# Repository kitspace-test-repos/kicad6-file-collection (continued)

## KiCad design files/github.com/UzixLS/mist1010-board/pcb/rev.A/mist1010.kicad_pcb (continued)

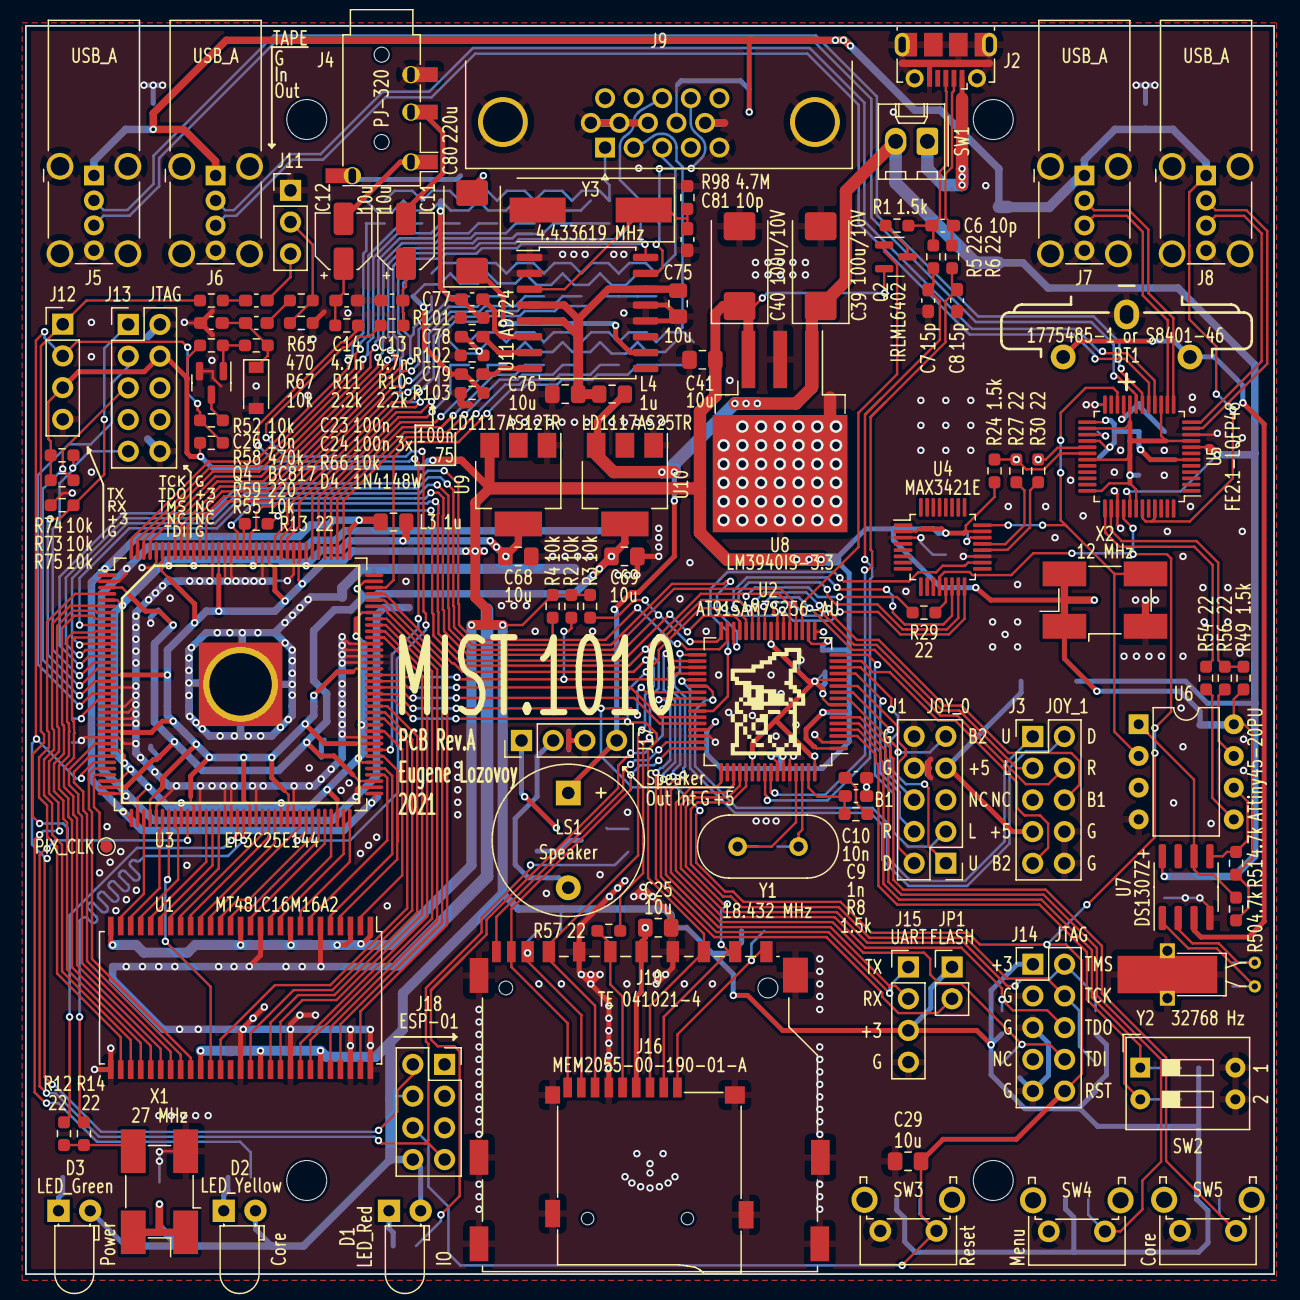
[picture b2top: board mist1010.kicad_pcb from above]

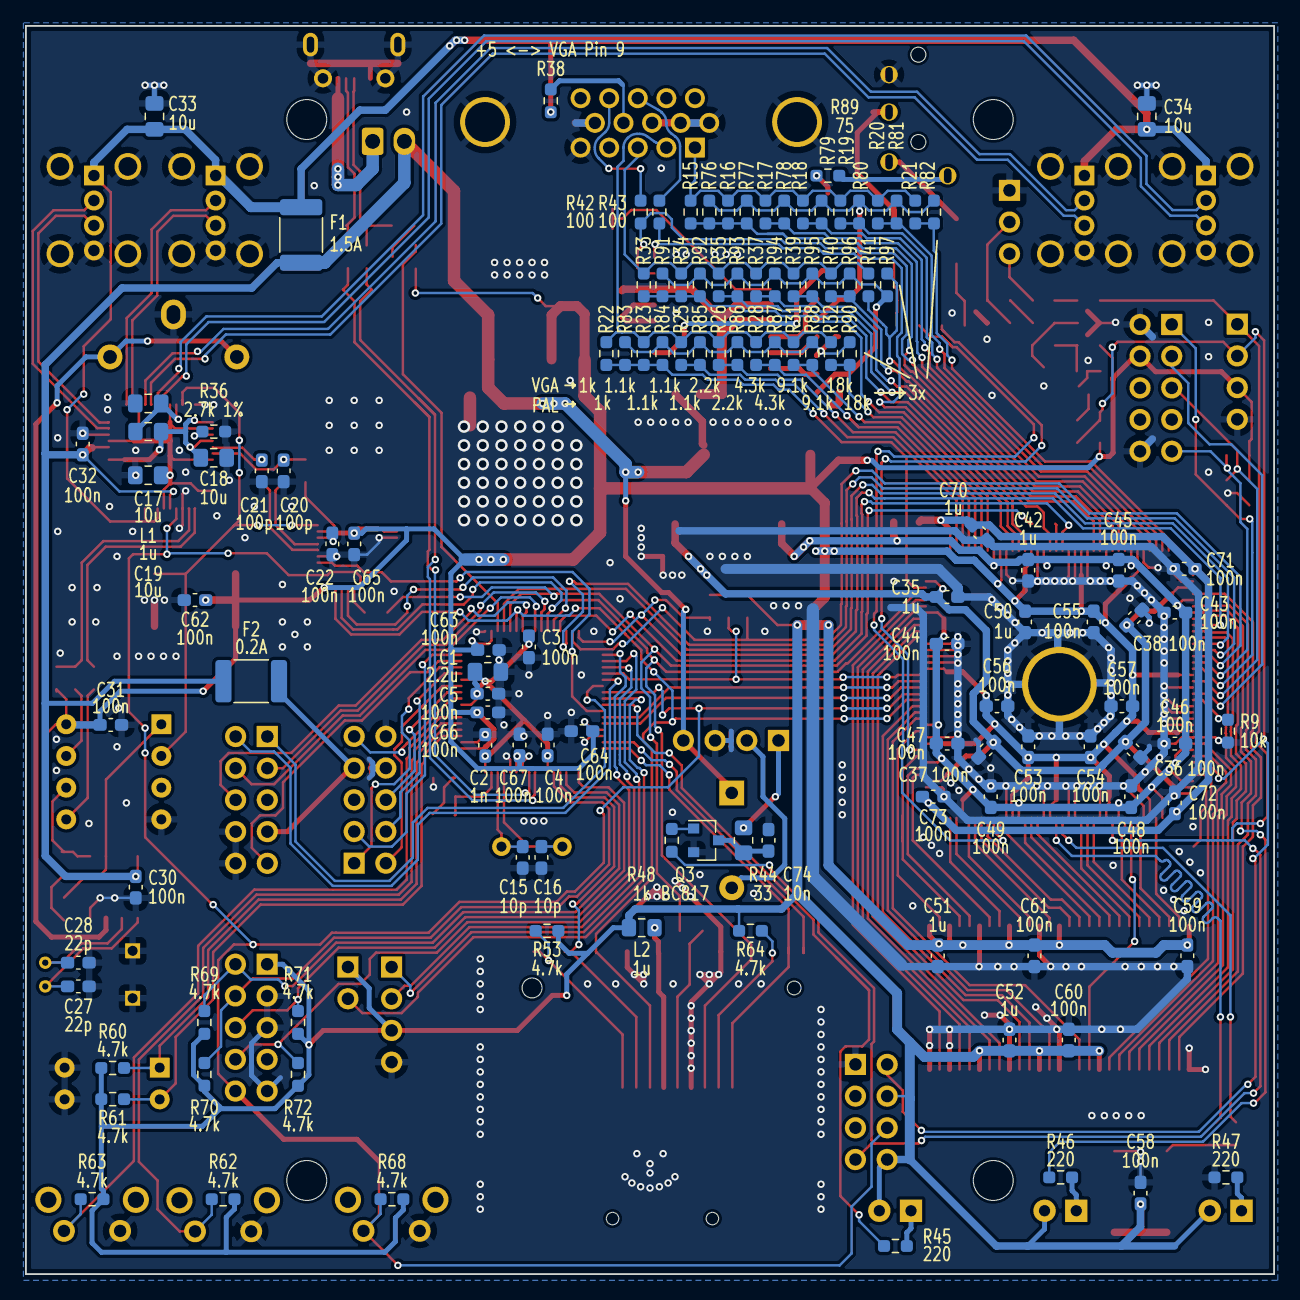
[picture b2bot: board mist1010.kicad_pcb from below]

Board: 2 copper layers, 100.0 x 100.0 mm, 242 parts (124 on the bottom side), 201 nets.

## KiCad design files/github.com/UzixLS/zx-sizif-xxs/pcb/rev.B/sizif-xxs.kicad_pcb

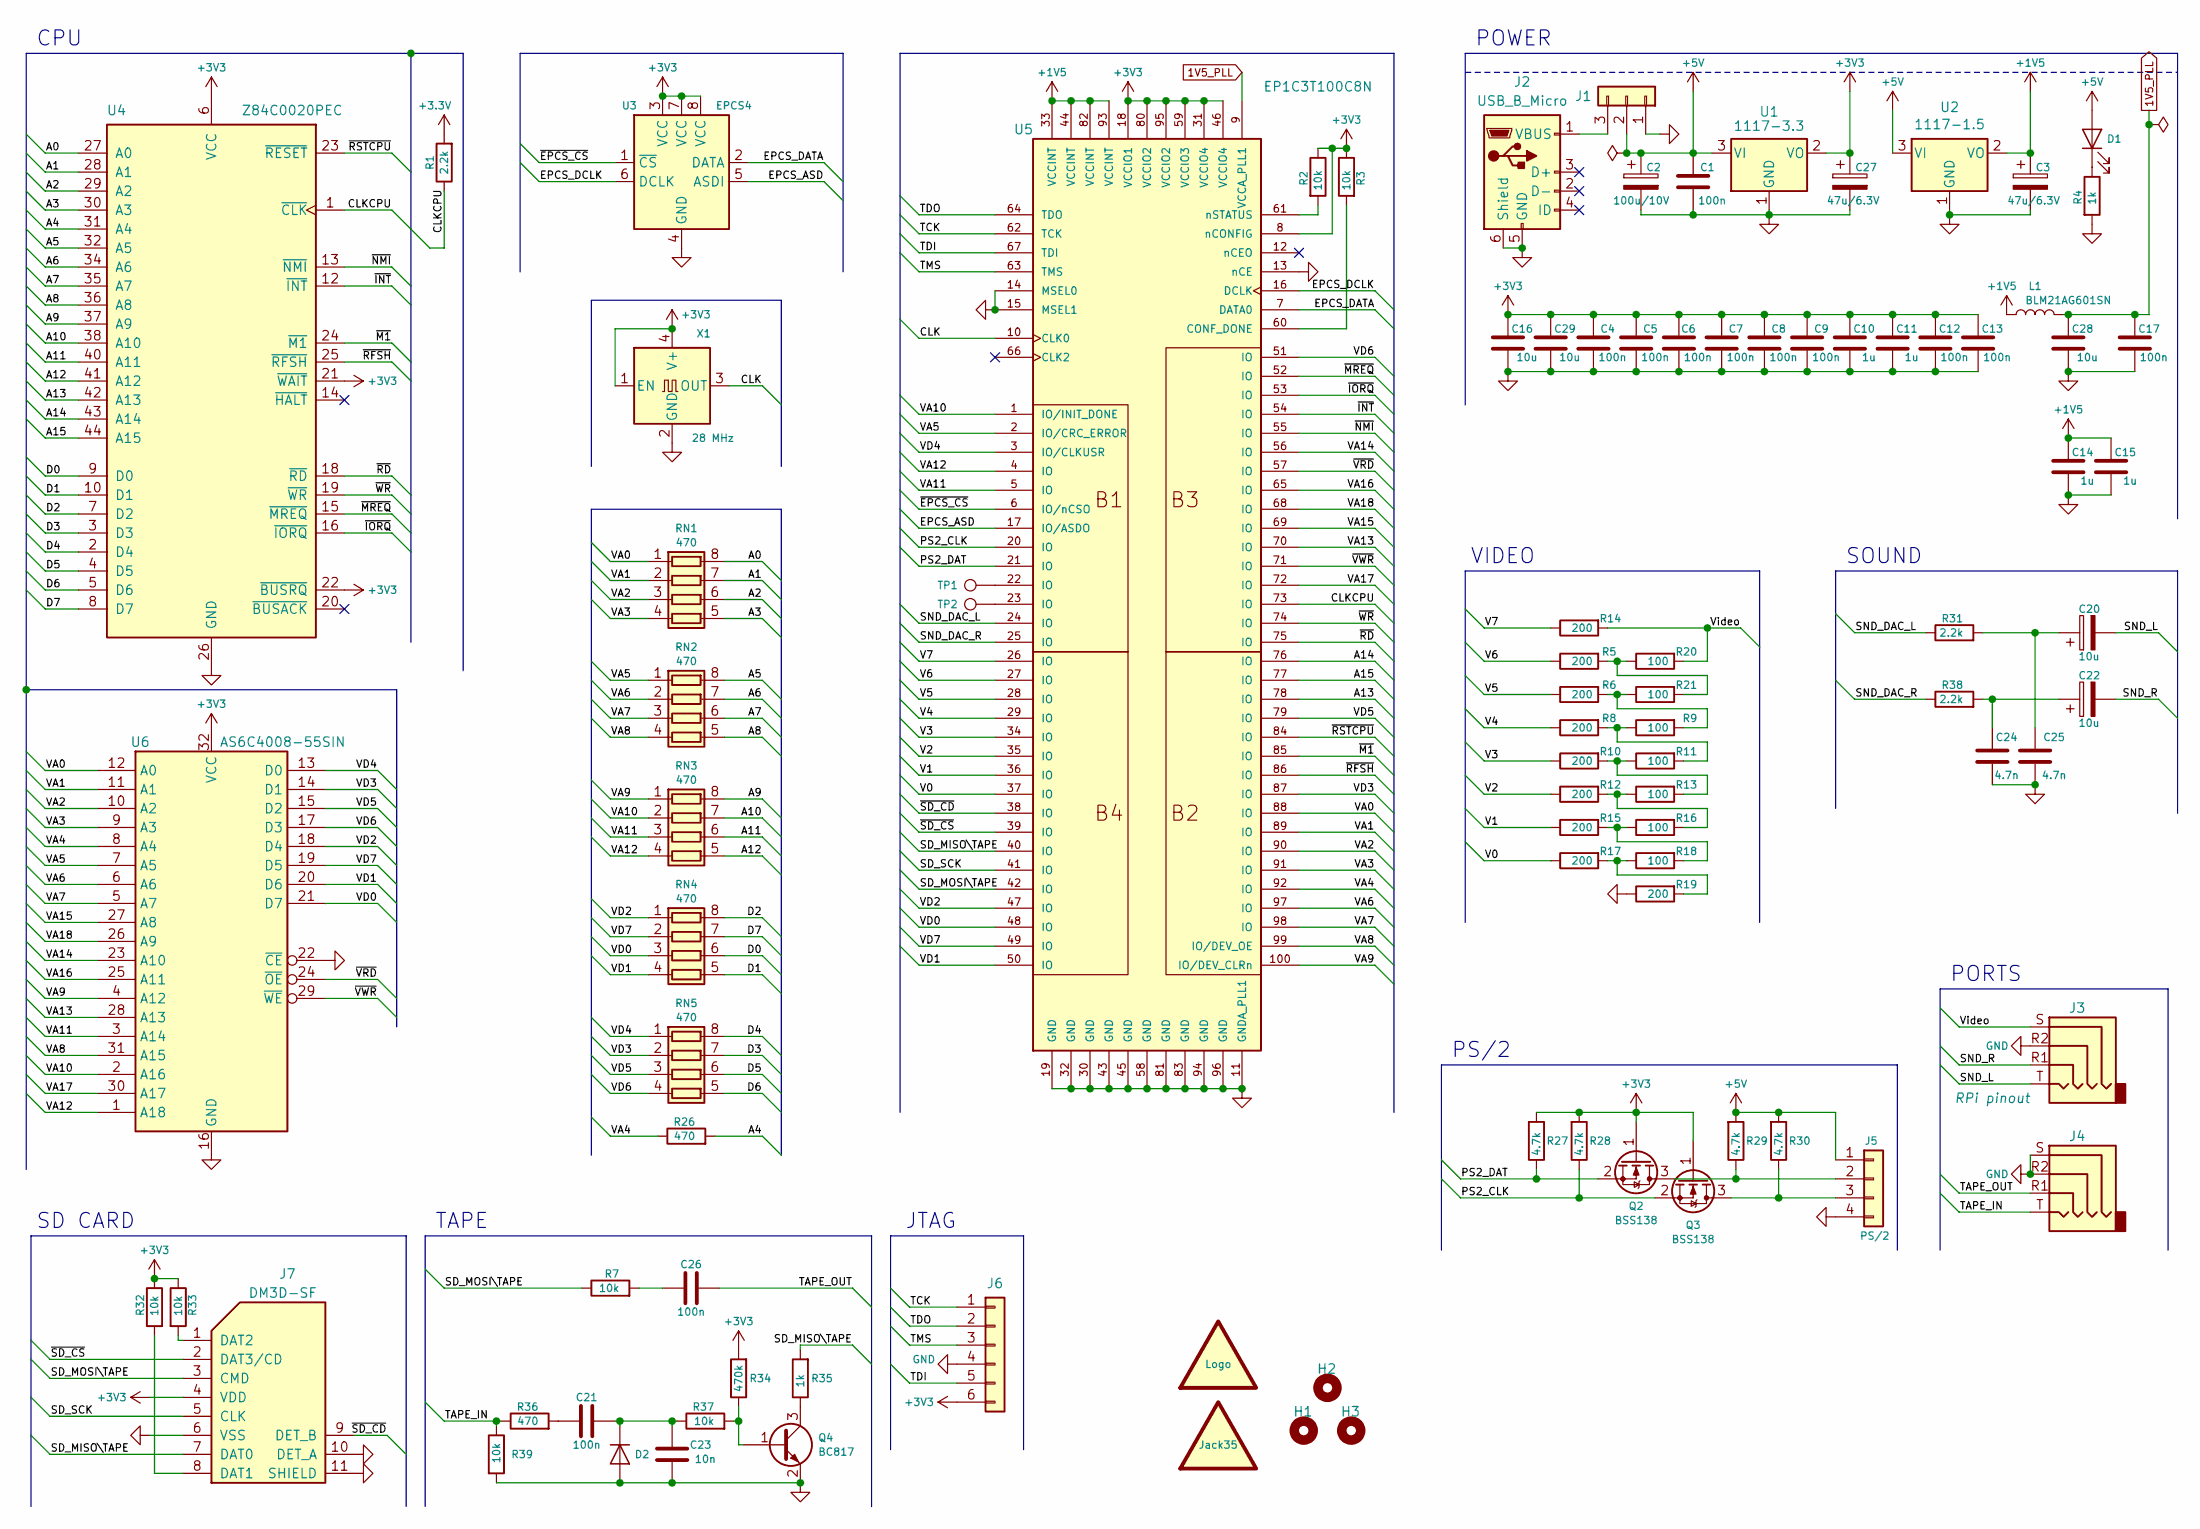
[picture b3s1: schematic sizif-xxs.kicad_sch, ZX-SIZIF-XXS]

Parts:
C1, C4, C6, C7, C8, C9, C12, C13, C17, C21, C26: 100n; C_0603_1608Metric_Pad1.08x0.95mm_HandSolder
C2: 100u/10V; CP_EIA-7343-31_Kemet-D_Pad2.25x2.55mm_HandSolder
C3, C27: 47u/6.3V; CP_EIA-3528-21_Kemet-B_Pad1.50x2.35mm_HandSolder
C5: 100n; C_0805_2012Metric_Pad1.18x1.45mm_HandSolder
C10, C11, C14, C15: 1u; C_0603_1608Metric_Pad1.08x0.95mm_HandSolder
C16, C28, C29: 10u; C_0805_2012Metric_Pad1.18x1.45mm_HandSolder
C20, C22: 10u; CP_EIA-3216-18_Kemet-A_Pad1.58x1.35mm_HandSolder
C23: 10n; C_0603_1608Metric_Pad1.08x0.95mm_HandSolder
C24, C25: 4.7n; C_0603_1608Metric_Pad1.08x0.95mm_HandSolder
D1: LED; LED_D4.0mm
D2: 1N4148W; D_SOD-123
H1, H2, H3: MountingHole; MountingHole_2.7mm_M2.5_dk5.0mm_Mask
J1: Pin header 1x3 Pitch=2.54mm; PinHeader_1x03_P2.54mm_Vertical
J2: USB_B_Micro; USB_Micro-B_Molex-105017-0001
J3, J4: PJ-320; PJ-320A_D
J5: Pin header 1x4 Pitch=2.54mm; PinHeader_1x04_P2.54mm_Vertical
J6: Solder points; PinPoints_1x06_P1.27mm
J7: DM3D-SF; microSD_HC_Hirose_DM3D-SF
L1: BLM21AG601SN; L_0805_2012Metric_Pad1.15x1.40mm_HandSolder
LOGO1: graphic; black-mage-9.6x6.5
LOGO2: Jack35; jack35_4pin
Q2, Q3: BSS138; SOT-23
Q4: BC817; SOT-23
R1, R31, R38: 2.2k; R_0603_1608Metric_Pad0.98x0.95mm_HandSolder
R2, R3, R7, R32, R33, R37, R39: 10k; R_0603_1608Metric_Pad0.98x0.95mm_HandSolder
R4, R35: 1k; R_0603_1608Metric_Pad0.98x0.95mm_HandSolder
R5, R6, R8, R10, R12, R14, R15, R17, R19: 200; R_0603_1608Metric_Pad0.98x0.95mm_HandSolder
R9, R11, R13, R16, R18, R20, R21: 100; R_0603_1608Metric_Pad0.98x0.95mm_HandSolder
R26, R36: 470; R_0603_1608Metric_Pad0.98x0.95mm_HandSolder
R27, R28, R29, R30: 4.7k; R_0603_1608Metric_Pad0.98x0.95mm_HandSolder
R34: 470k; R_0603_1608Metric_Pad0.98x0.95mm_HandSolder
RN1, RN2, RN3, RN4, RN5: 470; R_Array_Convex_4x0603
TP1, TP2: TestPoint; TestPoint_Pad_D1.0mm
U1: 1117-3.3; SOT-223-3_TabPin2
U2: 1117-1.5; SOT-223-3_TabPin2
U3: EPCS4; SOIC-8_3.9x4.9mm_P1.27mm
U4: Z84C0020PEC; TQFP-44_14x14mm_P0.8mm
U5: EP1C3T100C8N; TQFP-100_14x14mm_P0.5mm
U6: AS6C4008-55SIN; SSOP-32_11.305x20.495mm_P1.27mm
X1: 28 MHz; Oscillator_SMD_SeikoEpson_SG8002CA-4Pin_7.0x5.0mm

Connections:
1V5_PLL: C17.2, C28.2, L1.2, U5.9 (VCCA_PLL1)
+1V5: C3.1, C14.1, C15.2, L1.1, U2.2 (VO), U5.33 (VCCINT), U5.44 (VCCINT), U5.82 (VCCINT), U5.93 (VCCINT)
+5V: C1.2, C2.1, D1.2 (A), J1.2, J5.1, R29.2, R30.2, U1.3 (VI), U2.3 (VI)
/A0: RN1.8 (R1.2), U4.27 (A0)
/A1: RN1.7 (R2.2), U4.28 (A1)
/A2: RN1.6 (R3.2), U4.29 (A2)
/A3: RN1.5 (R4.2), U4.30 (A3)
/A4: R26.2, U4.31 (A4)
/A5: RN2.8 (R1.2), U4.32 (A5)
/A6: RN2.7 (R2.2), U4.34 (A6)
/A7: RN2.6 (R3.2), U4.35 (A7)
/A8: RN2.5 (R4.2), U4.36 (A8)
/A9: RN3.8 (R1.2), U4.37 (A9)
/A10: RN3.7 (R2.2), U4.38 (A10)
/A11: RN3.6 (R3.2), U4.40 (A11)
/A12: RN3.5 (R4.2), U4.41 (A12)
/A13: U4.42 (A13), U5.78 (IO)
/A14: U4.43 (A14), U5.76 (IO)
/A15: U4.44 (A15), U5.77 (IO)
/CLK: U5.10 (CLK0), X1.3 (OUT)
/CLKCPU: R1.1, U4.1 (~CLK~), U5.73 (IO)
/D0: RN4.6 (R3.2), U4.9 (D0)
/D1: RN4.5 (R4.2), U4.10 (D1)
/D2: RN4.8 (R1.2), U4.7 (D2)
/D3: RN5.7 (R2.2), U4.3 (D3)
/D4: RN5.8 (R1.2), U4.2 (D4)
/D5: RN5.6 (R3.2), U4.4 (D5)
/D6: RN5.5 (R4.2), U4.5 (D6)
/D7: RN4.7 (R2.2), U4.8 (D7)
/EPCS_ASD: U3.5 (ASDI), U5.17 (IO/ASDO)
/EPCS_DATA: U3.2 (DATA), U5.7 (DATA0)
/EPCS_DCLK: U3.6 (DCLK), U5.16 (DCLK)
/PS2_CLK: Q3.2 (S), R28.1, U5.20 (IO)
/PS2_DAT: Q2.2 (S), R27.1, U5.21 (IO)
/SD_MISO\TAPE: J7.7 (DAT0), R35.2, U5.40 (IO)
/SD_MOSI\TAPE: J7.3 (CMD), R7.1, U5.42 (IO)
/SD_SCK: J7.5 (CLK), U5.41 (IO)
/SND_DAC_L: R31.1, U5.24 (IO)
/SND_DAC_R: R38.1, U5.25 (IO)
/SND_L: C20.2, J3.T
/SND_R: C22.2, J3.R1
/TAPE_IN: J4.T, R36.1, R39.1
/TAPE_OUT: C26.1, J4.R1
/TCK: J6.1, U5.62 (TCK)
/TDI: J6.5, U5.67 (TDI)
/TDO: J6.2, U5.64 (TDO)
/TMS: J6.3, U5.63 (TMS)
/V0: R17.1, U5.37 (IO)
/V1: R15.1, U5.36 (IO)
/V2: R12.1, U5.35 (IO)
/V3: R10.1, U5.34 (IO)
/V4: R8.1, U5.29 (IO)
/V5: R6.1, U5.28 (IO)
/V6: R5.1, U5.27 (IO)
/V7: R14.1, U5.26 (IO)
/VA0: RN1.1 (R1.1), U5.88 (IO), U6.12 (A0)
/VA1: RN1.2 (R2.1), U5.89 (IO), U6.11 (A1)
/VA2: RN1.3 (R3.1), U5.90 (IO), U6.10 (A2)
/VA3: RN1.4 (R4.1), U5.91 (IO), U6.9 (A3)
/VA4: R26.1, U5.92 (IO), U6.8 (A4)
/VA5: RN2.1 (R1.1), U5.2 (IO/CRC_ERROR), U6.7 (A5)
/VA6: RN2.2 (R2.1), U5.97 (IO), U6.6 (A6)
/VA7: RN2.3 (R3.1), U5.98 (IO), U6.5 (A7)
/VA8: RN2.4 (R4.1), U5.99 (IO/DEV_OE), U6.31 (A15)
/VA9: RN3.1 (R1.1), U5.100 (IO/DEV_CLRn), U6.4 (A12)
/VA10: RN3.2 (R2.1), U5.1 (IO/INIT_DONE), U6.2 (A16)
/VA11: RN3.3 (R3.1), U5.5 (IO), U6.3 (A14)
/VA12: RN3.4 (R4.1), U5.4 (IO), U6.1 (A18)
/VA13: U5.70 (IO), U6.28 (A13)
/VA14: U5.56 (IO), U6.23 (A10)
/VA15: U5.69 (IO), U6.27 (A8)
/VA16: U5.65 (IO), U6.25 (A11)
/VA17: U5.72 (IO), U6.30 (A17)
/VA18: U5.68 (IO), U6.26 (A9)
/VD0: RN4.3 (R3.1), U5.48 (IO), U6.21 (D7)
/VD1: RN4.4 (R4.1), U5.50 (IO), U6.20 (D6)
/VD2: RN4.1 (R1.1), U5.47 (IO), U6.18 (D4)
/VD3: RN5.2 (R2.1), U5.87 (IO), U6.14 (D1)
/VD4: RN5.1 (R1.1), U5.3 (IO/CLKUSR), U6.13 (D0)
/VD5: RN5.3 (R3.1), U5.79 (IO), U6.15 (D2)
/VD6: RN5.4 (R4.1), U5.51 (IO), U6.17 (D3)
/VD7: RN4.2 (R2.1), U5.49 (IO), U6.19 (D5)
/Video: J3.S, R14.2, R20.2
/~EPCS_CS: U3.1 (~CS), U5.6 (IO/nCSO)
/~INT: U4.12 (~INT~), U5.54 (IO)
/~IORQ: U4.16 (~IORQ~), U5.53 (IO)
/~M1: U4.24 (~M1~), U5.85 (IO)
/~MREQ: U4.15 (~MREQ~), U5.52 (IO)
/~NMI: U4.13 (~NMI~), U5.55 (IO)
/~RD: U4.18 (~RD~), U5.75 (IO)
/~RFSH: U4.25 (~RFSH~), U5.86 (IO)
/~RSTCPU: U4.23 (~RESET~), U5.84 (IO)
/~SD_CD: J7.9 (DET_B), U5.38 (IO)
/~SD_CS: J7.2 (DAT3/CD), U5.39 (IO)
/~VRD: U5.57 (IO), U6.24 (~OE)
/~VWR: U5.71 (IO), U6.29 (~WE)
/~WR: U4.19 (~WR~), U5.74 (IO)
GND: C1.1, C2.2, C3.2, C4.1, C5.1, C6.2, C7.2, C8.2, C9.2, C10.2, C11.2, C12.2, C13.2, C14.2, C15.1, C16.1, C17.1, C23.2, C24.2, C25.2, C27.2, C28.1, C29.1, D2.2 (A), J1.1, J2.5 (GND), J2.6 (Shield), J3.R2, J4.R2, J4.S, J5.4, J6.4, J7.6 (VSS), J7.10 (DET_A), J7.11 (SHIELD), Q4.2 (E), R4.2, R19.1, R39.2, U1.1 (GND), U2.1 (GND), U3.4 (GND), U4.26 (GND), U5.11 (GNDA_PLL1), U5.13 (nCE), U5.14 (MSEL0), U5.15 (MSEL1), U5.19 (GND), U5.30 (GND), U5.32 (GND), U5.43 (GND), U5.45 (GND), U5.58 (GND), U5.81 (GND), U5.83 (GND), U5.94 (GND), U5.96 (GND), U6.16 (GND), U6.22 (~CE), X1.2 (GND)
unnamed: C20.1, C25.1, R31.2
unnamed: C21.1, C23.1, D2.1 (K), R37.1
unnamed: C21.2, R36.2
unnamed: C22.1, C24.1, R38.2
unnamed: C26.2, R7.2
unnamed: D1.1 (K), R4.1
unnamed: J1.3, J2.1 (VBUS)
unnamed: J5.2, Q2.3 (D), R29.1
unnamed: J5.3, Q3.3 (D), R30.1
unnamed: J7.1 (DAT2), R33.2
unnamed: J7.8 (DAT1), R32.2
unnamed: Q4.1 (B), R34.1, R37.2
unnamed: Q4.3 (C), R35.1
unnamed: R2.2, U5.61 (nSTATUS)
unnamed: R3.2, U5.60 (CONF_DONE)
unnamed: R10.2, R11.1, R13.2
unnamed: R8.2, R9.1, R11.2
unnamed: R12.2, R13.1, R16.2
unnamed: R15.2, R16.1, R18.2
unnamed: R17.2, R18.1, R19.2
unnamed: R5.2, R20.1, R21.2
unnamed: R6.2, R9.2, R21.1
unnamed: TP1.1, U5.22 (IO)
unnamed: TP2.1, U5.23 (IO)

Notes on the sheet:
CPU
SD CARD
TAPE
JTAG
PS/2
VIDEO
POWER
SOUND
PORTS

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
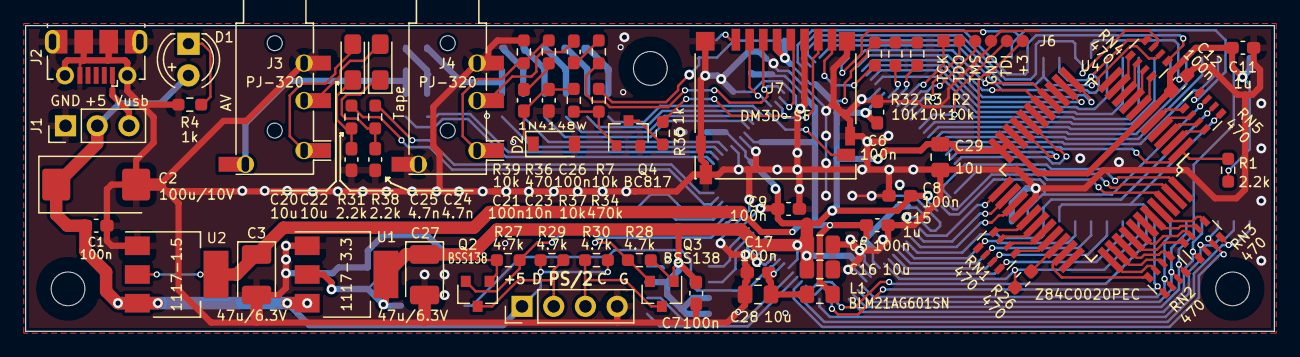
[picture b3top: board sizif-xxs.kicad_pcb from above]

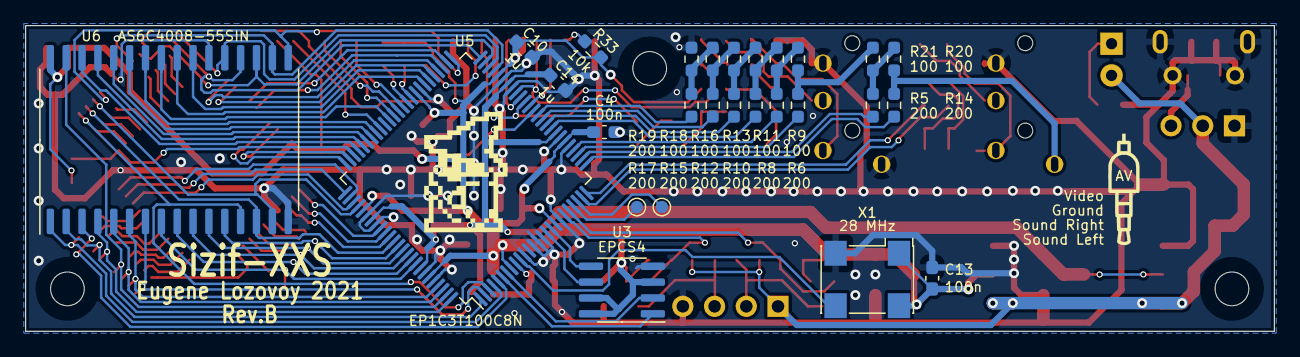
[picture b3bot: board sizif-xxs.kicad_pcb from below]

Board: 2 copper layers, 100.0 x 24.5 mm, 94 parts (29 on the bottom side), 123 nets.

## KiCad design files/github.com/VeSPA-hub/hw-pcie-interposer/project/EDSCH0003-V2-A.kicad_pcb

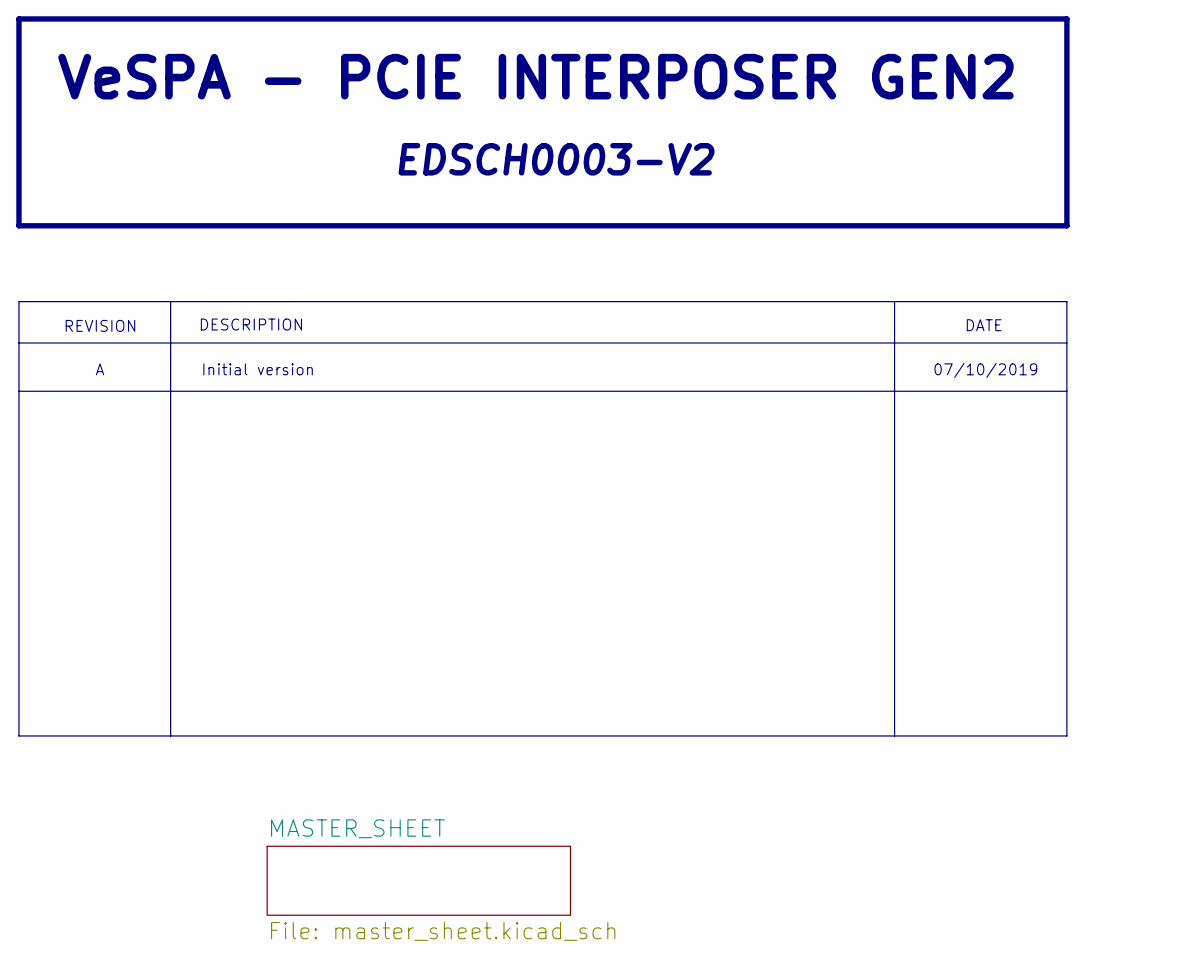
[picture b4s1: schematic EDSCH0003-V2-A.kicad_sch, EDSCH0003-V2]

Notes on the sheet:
VeSPA - PCIE INTERPOSER GEN2
REVISION
DESCRIPTION
Initial version
EDSCH0003-V2
DATE
07/10/2019

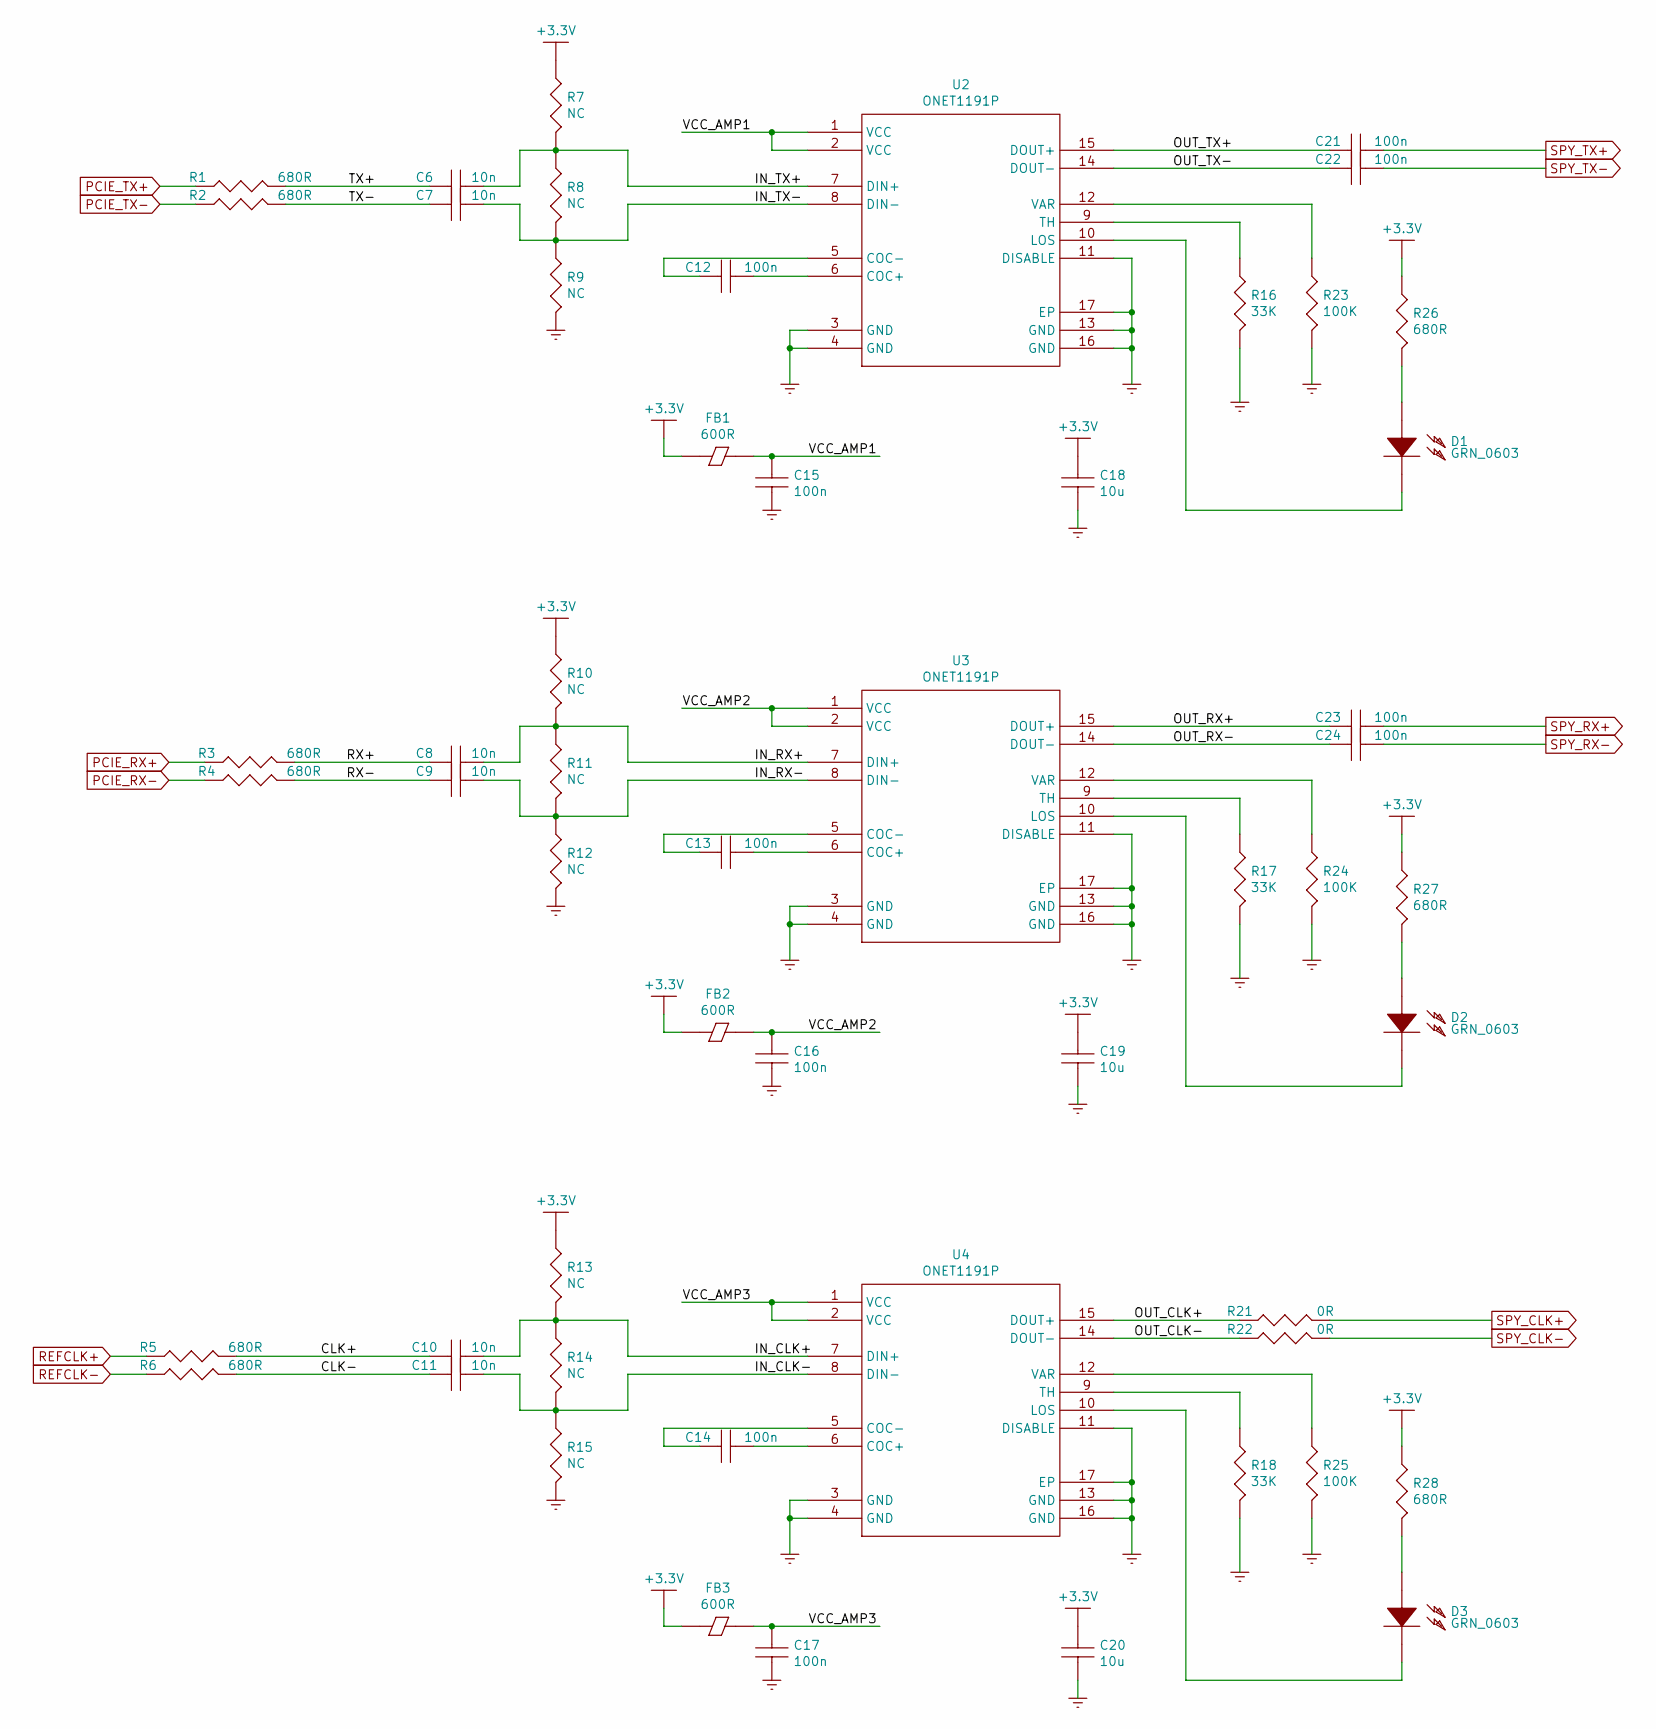
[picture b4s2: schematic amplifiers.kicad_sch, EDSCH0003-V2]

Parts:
C6, C7, C8, C9, C10, C11: C10N_0402; r_smt0402_ref
C12, C13, C14, C15, C16, C17, C21, C22, C23, C24: C100N_16V_0402; r_smt0402_ref
C18, C19, C20: C10U_50V_1206; c_smt1206_ref
D1, D2, D3: LED_GRN_0603; LED_0603_1608Metric_Castellated
FB1, FB2, FB3: FR_600R_0.2A_0402; r_smt0402_ref
R1, R2, R3, R4, R5, R6, R26, R27, R28: R680R_1%_0603; r_smt0603_ref
R7, R8, R9, R10, R11, R12, R13, R14, R15: R_NC_0402; r_smt0402_ref
R16, R17, R18: R33K_1%_0402; r_smt0402_ref
R21, R22: R0R_5%_0402; r_smt0402_ref
R23, R24, R25: R100K_1%_0402; r_smt0402_ref
U2, U3, U4: ONET1191P; QFN-16-1EP_3x3mm_P0.5mm_EP1.7x1.7mm

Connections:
+3.3V: C18.1, C19.1, C20.1, FB1.1, FB2.1, FB3.1, R7.1, R10.1, R13.1, R26.1, R27.1, R28.1; also elsewhere on the board
/MASTER_SHEET/AMPLIFIERS/CLK+: C10.1, R5.2
/MASTER_SHEET/AMPLIFIERS/CLK-: C11.1, R6.2
/MASTER_SHEET/AMPLIFIERS/IN_CLK+: C10.2, R13.2, R14.1, U4.7 (DIN+)
/MASTER_SHEET/AMPLIFIERS/IN_CLK-: C11.2, R14.2, R15.1, U4.8 (DIN-)
/MASTER_SHEET/AMPLIFIERS/IN_RX+: C8.2, R10.2, R11.1, U3.7 (DIN+)
/MASTER_SHEET/AMPLIFIERS/IN_RX-: C9.2, R11.2, R12.1, U3.8 (DIN-)
/MASTER_SHEET/AMPLIFIERS/IN_TX+: C6.2, R7.2, R8.1, U2.7 (DIN+)
/MASTER_SHEET/AMPLIFIERS/IN_TX-: C7.2, R8.2, R9.1, U2.8 (DIN-)
/MASTER_SHEET/AMPLIFIERS/OUT_CLK+: R21.1, U4.15 (DOUT+)
/MASTER_SHEET/AMPLIFIERS/OUT_CLK-: R22.1, U4.14 (DOUT-)
/MASTER_SHEET/AMPLIFIERS/OUT_RX+: C23.1, U3.15 (DOUT+)
/MASTER_SHEET/AMPLIFIERS/OUT_RX-: C24.1, U3.14 (DOUT-)
/MASTER_SHEET/AMPLIFIERS/OUT_TX+: C21.1, U2.15 (DOUT+)
/MASTER_SHEET/AMPLIFIERS/OUT_TX-: C22.1, U2.14 (DOUT-)
/MASTER_SHEET/AMPLIFIERS/RX+: C8.1, R3.2
/MASTER_SHEET/AMPLIFIERS/RX-: C9.1, R4.2
/MASTER_SHEET/AMPLIFIERS/TX+: C6.1, R1.2
/MASTER_SHEET/AMPLIFIERS/TX-: C7.1, R2.2
/MASTER_SHEET/AMPLIFIERS/VCC_AMP1: C15.1, FB1.2, U2.1 (VCC), U2.2 (VCC)
/MASTER_SHEET/AMPLIFIERS/VCC_AMP2: C16.1, FB2.2, U3.1 (VCC), U3.2 (VCC)
/MASTER_SHEET/AMPLIFIERS/VCC_AMP3: C17.1, FB3.2, U4.1 (VCC), U4.2 (VCC)
GND: C15.2, C16.2, C17.2, C18.2, C19.2, C20.2, R9.2, R12.2, R15.2, R16.2, R17.2, R18.2, R23.2, R24.2, R25.2, U2.3 (GND), U2.4 (GND), U2.11 (DISABLE), U2.13 (GND), U2.16 (GND), U2.17 (EP), U3.3 (GND), U3.4 (GND), U3.11 (DISABLE), U3.13 (GND), U3.16 (GND), U3.17 (EP), U4.3 (GND), U4.4 (GND), U4.11 (DISABLE), U4.13 (GND), U4.16 (GND), U4.17 (EP); also elsewhere on the board
unnamed: C12.1, U2.5 (COC-)
unnamed: C12.2, U2.6 (COC+)
unnamed: C13.1, U3.5 (COC-)
unnamed: C13.2, U3.6 (COC+)
unnamed: C14.1, U4.5 (COC-)
unnamed: C14.2, U4.6 (COC+)
unnamed: D1.1 (A), R26.2
unnamed: D1.2 (K), U2.10 (LOS)
unnamed: D2.1 (A), R27.2
unnamed: D2.2 (K), U3.10 (LOS)
unnamed: D3.1 (A), R28.2
unnamed: D3.2 (K), U4.10 (LOS)
unnamed: R16.1, U2.9 (TH)
unnamed: R17.1, U3.9 (TH)
unnamed: R18.1, U4.9 (TH)
unnamed: R23.1, U2.12 (VAR)
unnamed: R24.1, U3.12 (VAR)
unnamed: R25.1, U4.12 (VAR)
PCIE_RX+: R3.1; also elsewhere on the board
PCIE_RX-: R4.1; also elsewhere on the board
PCIE_TX+: R1.1; also elsewhere on the board
PCIE_TX-: R2.1; also elsewhere on the board
REFCLK+: R5.1; also elsewhere on the board
REFCLK-: R6.1; also elsewhere on the board
SPY_CLK+: R21.2; also elsewhere on the board
SPY_CLK-: R22.2; also elsewhere on the board
SPY_RX+: C23.2; also elsewhere on the board
SPY_RX-: C24.2; also elsewhere on the board
SPY_TX+: C21.2; also elsewhere on the board
SPY_TX-: C22.2; also elsewhere on the board
